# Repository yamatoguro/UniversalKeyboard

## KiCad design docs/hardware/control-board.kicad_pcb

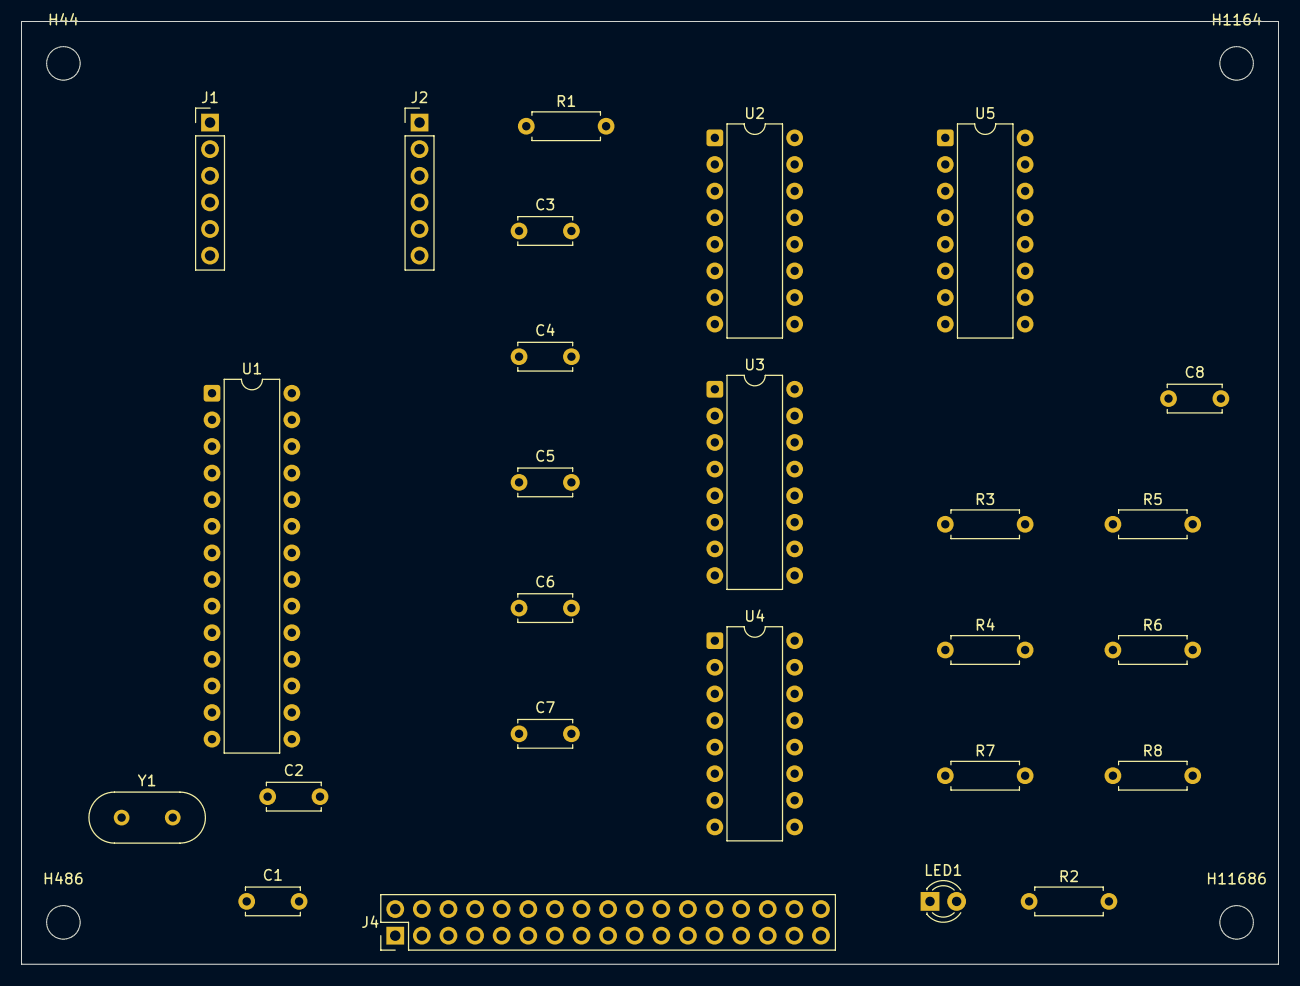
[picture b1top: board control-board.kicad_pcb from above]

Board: 2 copper layers, 120.0 x 90.0 mm, 30 parts (0 on the bottom side), 45 nets, no tracks yet.

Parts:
C1, C2: 22pF; C_Disc_D5.0mm_W2.5mm_P5.00mm
C3, C4, C5, C6, C8: 100nF; C_Disc_D5.0mm_W2.5mm_P5.00mm
C7: 10uF; C_Disc_D5.0mm_W2.5mm_P5.00mm
H44, H486, H1164, H11686: MountingHole; MountingHole_3.2mm_M3
J1, J2: Conn_01x06; PinHeader_1x06_P2.54mm_Vertical
J4: Conn_02x17; PinHeader_2x17_P2.54mm_Vertical
LED1: LED; LED_D3.0mm
R1, R3, R4, R5, R6, R7, R8: 10k; R_Axial_DIN0207_L6.3mm_D2.5mm_P7.62mm_Horizontal
R2: 330R; R_Axial_DIN0207_L6.3mm_D2.5mm_P7.62mm_Horizontal
U1: ATmega328P-PU; DIP-28_W7.62mm
U2, U3, U4: 74HC595; DIP-16_W7.62mm
U5: 74HC165; DIP-16_W7.62mm
Y1: 8MHz; Crystal_HC49-U_Vertical

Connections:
3V3: C3.1, C4.1, C5.1, C6.1, C7.1, C8.1, J1.1, J2.2, J4.30, R1.1, U1.7, U1.20, U1.21, U2.10, U2.16, U3.10, U3.16, U4.10, U4.16, U5.16
COL0: J4.1, U2.15
COL1: J4.2, U2.1
COL2: J4.3, U2.2
COL3: J4.4, U2.3
COL4: J4.5, U2.4
COL5: J4.6, U2.5
COL6: J4.7, U2.6
COL7: J4.8, U2.7
COL8: J4.9, U3.15
COL9: J4.10, U3.1
COL10: J4.11, U3.2
COL11: J4.12, U3.3
COL12: J4.13, U3.4
COL13: J4.14, U3.5
COL14: J4.15, U3.6
COL15: J4.16, U3.7
COL16: J4.17, U4.15
COL17: J4.18, U4.1
COL18: J4.19, U4.2
COL19: J4.20, U4.3
COL20: J4.21, U4.4
COL21: J4.22, U4.5
COL22: J4.23, U4.6
GND: C1.2, C2.2, C3.2, C4.2, C5.2, C6.2, C7.2, C8.2, J1.2, J1.6, J2.3, J4.31, J4.32, J4.33, LED1.1, R3.2, R4.2, R5.2, R6.2, R7.2, R8.2, U1.8, U1.22, U2.8, U2.13, U3.8, U3.13, U4.8, U4.13, U5.5, U5.6, U5.8, U5.10, U5.15
LED_A: LED1.2, R2.2
PI_RX: J1.4, U1.3
PI_TX: J1.3, U1.2
RESET: J2.1, R1.2, U1.1
ROW0: J4.24, R3.1, U5.11
ROW1: J4.25, R4.1, U5.12
ROW2: J4.26, R5.1, U5.13
ROW3: J4.27, R6.1, U5.14
ROW4: J4.28, R7.1, U5.3
ROW5: J4.29, R8.1, U5.4
SR_CASCADE1: U2.9, U3.14
SR_CASCADE2: U3.9, U4.14
SR_CLK: U1.5, U2.11, U3.11, U4.11, U5.2
SR_DATA_IN: U1.12, U5.9
SR_DS: U1.4, U2.14
SR_LATCH: U1.6, U2.12, U3.12, U4.12
SR_LOAD: U1.11, U5.1
STATUS_LED: R2.1, U1.14
XTAL1: C1.1, U1.9, Y1.1
XTAL2: C2.1, U1.10, Y1.2

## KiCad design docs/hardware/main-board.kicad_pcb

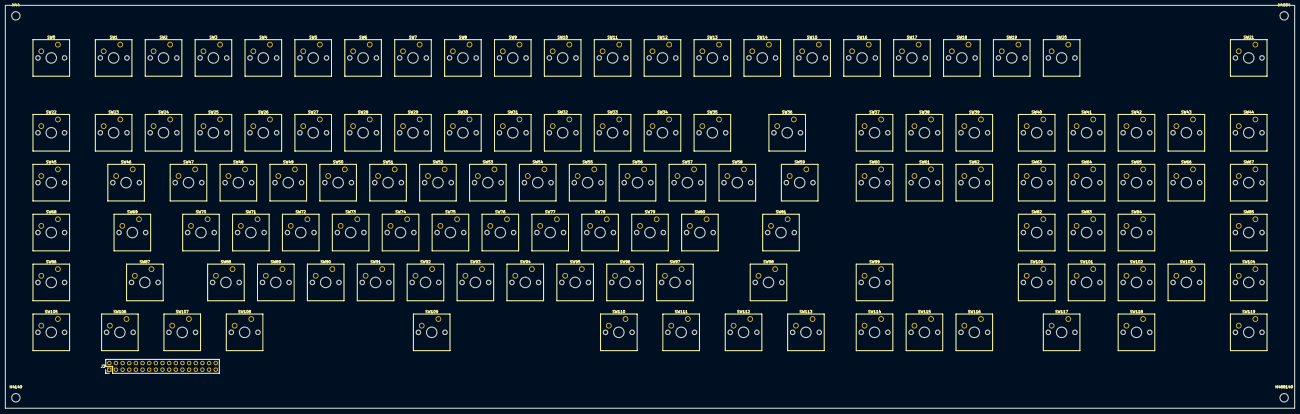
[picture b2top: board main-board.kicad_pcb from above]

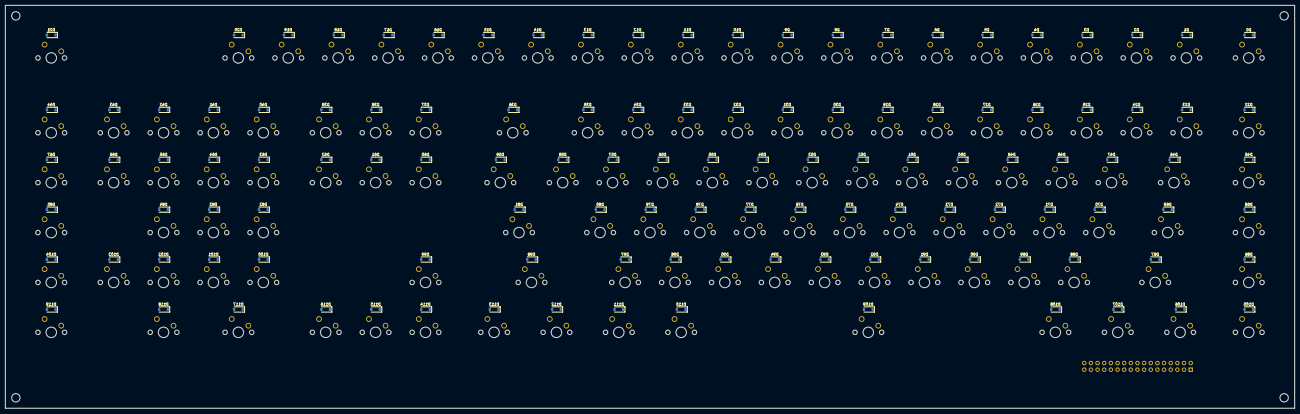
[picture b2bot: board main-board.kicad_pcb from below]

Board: 2 copper layers, 492.2 x 153.8 mm, 245 parts (120 on the bottom side), 150 nets, no tracks yet.

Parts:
D0, D1, D2, D3, D4, D5, D6, D7, D8, D9, D10, D11, D12, D13, D14, D15, D16, D17, D18, D19, D20, D21, D22, D23, D24, D25, D26, D27, D28, D29, D30, D31, D32, D33, D34, D35, D36, D37, D38, D39, D40, D41, D42, D43, D44, D45, D46, D47, D48, D49, D50, D51, D52, D53, D54, D55, D56, D57, D58, D59, D60, D61, D62, D63, D64, D65, D66, D67, D68, D69, D70, D71, D72, D73, D74, D75, D76, D77, D78, D79, D80, D81, D82, D83, D84, D85, D86, D87, D88, D89, D90, D91, D92, D93, D94, D95, D96, D97, D98, D99, D100, D101, D102, D103, D104, D105, D106, D107, D108, D109, D110, D111, D112, D113, D114, D115, D116, D117, D118, D119: BAT54; D_SOD-123
H44, H4149, H4884, H488149: MountingHole; MountingHole_3.2mm_M3
J3: Conn_02x17; PinHeader_2x17_P2.54mm_Vertical
SW0: K_000; SW_Cherry_MX_1.00u_PCB
SW1: K_001; SW_Cherry_MX_1.00u_PCB
SW2: K_002; SW_Cherry_MX_1.00u_PCB
SW3: K_003; SW_Cherry_MX_1.00u_PCB
SW4: K_004; SW_Cherry_MX_1.00u_PCB
SW5: K_005; SW_Cherry_MX_1.00u_PCB
SW6: K_006; SW_Cherry_MX_1.00u_PCB
SW7: K_007; SW_Cherry_MX_1.00u_PCB
SW8: K_008; SW_Cherry_MX_1.00u_PCB
SW9: K_009; SW_Cherry_MX_1.00u_PCB
SW10: K_010; SW_Cherry_MX_1.00u_PCB
SW11: K_011; SW_Cherry_MX_1.00u_PCB
SW12: K_012; SW_Cherry_MX_1.00u_PCB
SW13: K_013; SW_Cherry_MX_1.00u_PCB
SW14: K_014; SW_Cherry_MX_1.00u_PCB
SW15: K_015; SW_Cherry_MX_1.00u_PCB
SW16: K_016; SW_Cherry_MX_1.00u_PCB
SW17: K_017; SW_Cherry_MX_1.00u_PCB
SW18: K_018; SW_Cherry_MX_1.00u_PCB
SW19: K_019; SW_Cherry_MX_1.00u_PCB
SW20: K_020; SW_Cherry_MX_1.00u_PCB
SW21: K_021; SW_Cherry_MX_1.00u_PCB
SW22: K_022; SW_Cherry_MX_1.00u_PCB
SW23: K_023; SW_Cherry_MX_1.00u_PCB
SW24: K_024; SW_Cherry_MX_1.00u_PCB
SW25: K_025; SW_Cherry_MX_1.00u_PCB
SW26: K_026; SW_Cherry_MX_1.00u_PCB
SW27: K_027; SW_Cherry_MX_1.00u_PCB
SW28: K_028; SW_Cherry_MX_1.00u_PCB
SW29: K_029; SW_Cherry_MX_1.00u_PCB
SW30: K_030; SW_Cherry_MX_1.00u_PCB
SW31: K_031; SW_Cherry_MX_1.00u_PCB
SW32: K_032; SW_Cherry_MX_1.00u_PCB
SW33: K_033; SW_Cherry_MX_1.00u_PCB
SW34: K_034; SW_Cherry_MX_1.00u_PCB
SW35: K_035; SW_Cherry_MX_1.00u_PCB
SW36: K_036; SW_Cherry_MX_1.00u_PCB
SW37: K_037; SW_Cherry_MX_1.00u_PCB
SW38: K_038; SW_Cherry_MX_1.00u_PCB
SW39: K_039; SW_Cherry_MX_1.00u_PCB
SW40: K_040; SW_Cherry_MX_1.00u_PCB
SW41: K_041; SW_Cherry_MX_1.00u_PCB
SW42: K_042; SW_Cherry_MX_1.00u_PCB
SW43: K_043; SW_Cherry_MX_1.00u_PCB
SW44: K_044; SW_Cherry_MX_1.00u_PCB
SW45: K_045; SW_Cherry_MX_1.00u_PCB
SW46: K_046; SW_Cherry_MX_1.00u_PCB
SW47: K_047; SW_Cherry_MX_1.00u_PCB
SW48: K_048; SW_Cherry_MX_1.00u_PCB
SW49: K_049; SW_Cherry_MX_1.00u_PCB
SW50: K_050; SW_Cherry_MX_1.00u_PCB
SW51: K_051; SW_Cherry_MX_1.00u_PCB
SW52: K_052; SW_Cherry_MX_1.00u_PCB
SW53: K_053; SW_Cherry_MX_1.00u_PCB
SW54: K_054; SW_Cherry_MX_1.00u_PCB
SW55: K_055; SW_Cherry_MX_1.00u_PCB
SW56: K_056; SW_Cherry_MX_1.00u_PCB
SW57: K_057; SW_Cherry_MX_1.00u_PCB
SW58: K_058; SW_Cherry_MX_1.00u_PCB
SW59: K_059; SW_Cherry_MX_1.00u_PCB
SW60: K_060; SW_Cherry_MX_1.00u_PCB
SW61: K_061; SW_Cherry_MX_1.00u_PCB
SW62: K_062; SW_Cherry_MX_1.00u_PCB
SW63: K_063; SW_Cherry_MX_1.00u_PCB
SW64: K_064; SW_Cherry_MX_1.00u_PCB
SW65: K_065; SW_Cherry_MX_1.00u_PCB
SW66: K_066; SW_Cherry_MX_1.00u_PCB
SW67: K_067; SW_Cherry_MX_1.00u_PCB
SW68: K_068; SW_Cherry_MX_1.00u_PCB
SW69: K_069; SW_Cherry_MX_1.00u_PCB
SW70: K_070; SW_Cherry_MX_1.00u_PCB
SW71: K_071; SW_Cherry_MX_1.00u_PCB
SW72: K_072; SW_Cherry_MX_1.00u_PCB
SW73: K_073; SW_Cherry_MX_1.00u_PCB
SW74: K_074; SW_Cherry_MX_1.00u_PCB
SW75: K_075; SW_Cherry_MX_1.00u_PCB
SW76: K_076; SW_Cherry_MX_1.00u_PCB
SW77: K_077; SW_Cherry_MX_1.00u_PCB
SW78: K_078; SW_Cherry_MX_1.00u_PCB
SW79: K_079; SW_Cherry_MX_1.00u_PCB
SW80: K_080; SW_Cherry_MX_1.00u_PCB
SW81: K_081; SW_Cherry_MX_1.00u_PCB
SW82: K_082; SW_Cherry_MX_1.00u_PCB
SW83: K_083; SW_Cherry_MX_1.00u_PCB
SW84: K_084; SW_Cherry_MX_1.00u_PCB
SW85: K_085; SW_Cherry_MX_1.00u_PCB
SW86: K_086; SW_Cherry_MX_1.00u_PCB
SW87: K_087; SW_Cherry_MX_1.00u_PCB
SW88: K_088; SW_Cherry_MX_1.00u_PCB
SW89: K_089; SW_Cherry_MX_1.00u_PCB
SW90: K_090; SW_Cherry_MX_1.00u_PCB
SW91: K_091; SW_Cherry_MX_1.00u_PCB
SW92: K_092; SW_Cherry_MX_1.00u_PCB
SW93: K_093; SW_Cherry_MX_1.00u_PCB
SW94: K_094; SW_Cherry_MX_1.00u_PCB
SW95: K_095; SW_Cherry_MX_1.00u_PCB
SW96: K_096; SW_Cherry_MX_1.00u_PCB
SW97: K_097; SW_Cherry_MX_1.00u_PCB
SW98: K_098; SW_Cherry_MX_1.00u_PCB
SW99: K_099; SW_Cherry_MX_1.00u_PCB
SW100: K_100; SW_Cherry_MX_1.00u_PCB
SW101: K_101; SW_Cherry_MX_1.00u_PCB
SW102: K_102; SW_Cherry_MX_1.00u_PCB
SW103: K_103; SW_Cherry_MX_1.00u_PCB
SW104: K_104; SW_Cherry_MX_1.00u_PCB
SW105: K_105; SW_Cherry_MX_1.00u_PCB
SW106: K_106; SW_Cherry_MX_1.00u_PCB
SW107: K_107; SW_Cherry_MX_1.00u_PCB
SW108: K_108; SW_Cherry_MX_1.00u_PCB
SW109: K_109; SW_Cherry_MX_1.00u_PCB
SW110: K_110; SW_Cherry_MX_1.00u_PCB
SW111: K_111; SW_Cherry_MX_1.00u_PCB
SW112: K_112; SW_Cherry_MX_1.00u_PCB
SW113: K_113; SW_Cherry_MX_1.00u_PCB
SW114: K_114; SW_Cherry_MX_1.00u_PCB
SW115: K_115; SW_Cherry_MX_1.00u_PCB
SW116: K_116; SW_Cherry_MX_1.00u_PCB
SW117: K_117; SW_Cherry_MX_1.00u_PCB
SW118: K_118; SW_Cherry_MX_1.00u_PCB
SW119: K_119; SW_Cherry_MX_1.00u_PCB

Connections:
COL0: J3.1, SW0.1, SW22.1, SW45.1, SW68.1, SW86.1, SW105.1
COL1: J3.2, SW1.1, SW23.1, SW46.1, SW69.1, SW87.1, SW106.1
COL2: J3.3, SW2.1, SW24.1, SW47.1, SW70.1, SW88.1, SW107.1
COL3: J3.4, SW3.1, SW25.1, SW48.1, SW71.1, SW89.1, SW108.1
COL4: J3.5, SW4.1, SW26.1, SW49.1, SW72.1, SW90.1, SW109.1
COL5: J3.6, SW5.1, SW27.1, SW50.1, SW73.1, SW91.1, SW110.1
COL6: J3.7, SW6.1, SW28.1, SW51.1, SW74.1, SW92.1, SW111.1
COL7: J3.8, SW7.1, SW29.1, SW52.1, SW75.1, SW93.1, SW112.1
COL8: J3.9, SW8.1, SW30.1, SW53.1, SW76.1, SW94.1, SW113.1
COL9: J3.10, SW9.1, SW31.1, SW54.1, SW77.1, SW95.1, SW114.1
COL10: J3.11, SW10.1, SW32.1, SW55.1, SW78.1, SW96.1, SW115.1
COL11: J3.12, SW11.1, SW33.1, SW56.1, SW79.1, SW97.1, SW116.1
COL12: J3.13, SW12.1, SW34.1, SW57.1, SW80.1, SW98.1, SW117.1
COL13: J3.14, SW13.1, SW35.1, SW58.1, SW81.1, SW99.1, SW118.1
COL14: J3.15, SW14.1, SW36.1, SW59.1, SW82.1, SW100.1, SW119.1
COL15: J3.16, SW15.1, SW37.1, SW60.1, SW83.1, SW101.1
COL16: J3.17, SW16.1, SW38.1, SW61.1, SW84.1, SW102.1
COL17: J3.18, SW17.1, SW39.1, SW62.1, SW85.1, SW103.1
COL18: J3.19, SW18.1, SW40.1, SW63.1, SW104.1
COL19: J3.20, SW19.1, SW41.1, SW64.1
COL20: J3.21, SW20.1, SW42.1, SW65.1
COL21: J3.22, SW21.1, SW43.1, SW66.1
COL22: J3.23, SW44.1, SW67.1
GND: J3.31, J3.32, J3.33
KEY0: D0.2, SW0.2
KEY1: D1.2, SW1.2
KEY2: D2.2, SW2.2
KEY3: D3.2, SW3.2
KEY4: D4.2, SW4.2
KEY5: D5.2, SW5.2
KEY6: D6.2, SW6.2
KEY7: D7.2, SW7.2
KEY8: D8.2, SW8.2
KEY9: D9.2, SW9.2
KEY10: D10.2, SW10.2
KEY11: D11.2, SW11.2
KEY12: D12.2, SW12.2
KEY13: D13.2, SW13.2
KEY14: D14.2, SW14.2
KEY15: D15.2, SW15.2
KEY16: D16.2, SW16.2
KEY17: D17.2, SW17.2
KEY18: D18.2, SW18.2
KEY19: D19.2, SW19.2
KEY20: D20.2, SW20.2
KEY21: D21.2, SW21.2
KEY22: D22.2, SW22.2
KEY23: D23.2, SW23.2
KEY24: D24.2, SW24.2
KEY25: D25.2, SW25.2
KEY26: D26.2, SW26.2
KEY27: D27.2, SW27.2
KEY28: D28.2, SW28.2
KEY29: D29.2, SW29.2
KEY30: D30.2, SW30.2
KEY31: D31.2, SW31.2
KEY32: D32.2, SW32.2
KEY33: D33.2, SW33.2
KEY34: D34.2, SW34.2
KEY35: D35.2, SW35.2
KEY36: D36.2, SW36.2
KEY37: D37.2, SW37.2
KEY38: D38.2, SW38.2
KEY39: D39.2, SW39.2
KEY40: D40.2, SW40.2
KEY41: D41.2, SW41.2
KEY42: D42.2, SW42.2
KEY43: D43.2, SW43.2
KEY44: D44.2, SW44.2
KEY45: D45.2, SW45.2
KEY46: D46.2, SW46.2
KEY47: D47.2, SW47.2
KEY48: D48.2, SW48.2
KEY49: D49.2, SW49.2
KEY50: D50.2, SW50.2
KEY51: D51.2, SW51.2
KEY52: D52.2, SW52.2
KEY53: D53.2, SW53.2
KEY54: D54.2, SW54.2
KEY55: D55.2, SW55.2
KEY56: D56.2, SW56.2
KEY57: D57.2, SW57.2
KEY58: D58.2, SW58.2
KEY59: D59.2, SW59.2
KEY60: D60.2, SW60.2
KEY61: D61.2, SW61.2
KEY62: D62.2, SW62.2
KEY63: D63.2, SW63.2
KEY64: D64.2, SW64.2
KEY65: D65.2, SW65.2
KEY66: D66.2, SW66.2
KEY67: D67.2, SW67.2
KEY68: D68.2, SW68.2
KEY69: D69.2, SW69.2
KEY70: D70.2, SW70.2
KEY71: D71.2, SW71.2
KEY72: D72.2, SW72.2
KEY73: D73.2, SW73.2
KEY74: D74.2, SW74.2
KEY75: D75.2, SW75.2
KEY76: D76.2, SW76.2
KEY77: D77.2, SW77.2
KEY78: D78.2, SW78.2
KEY79: D79.2, SW79.2
KEY80: D80.2, SW80.2
KEY81: D81.2, SW81.2
KEY82: D82.2, SW82.2
KEY83: D83.2, SW83.2
KEY84: D84.2, SW84.2
KEY85: D85.2, SW85.2
KEY86: D86.2, SW86.2
KEY87: D87.2, SW87.2
KEY88: D88.2, SW88.2
KEY89: D89.2, SW89.2
KEY90: D90.2, SW90.2
KEY91: D91.2, SW91.2
KEY92: D92.2, SW92.2
KEY93: D93.2, SW93.2
KEY94: D94.2, SW94.2
KEY95: D95.2, SW95.2
KEY96: D96.2, SW96.2
KEY97: D97.2, SW97.2
KEY98: D98.2, SW98.2
KEY99: D99.2, SW99.2
KEY100: D100.2, SW100.2
KEY101: D101.2, SW101.2
KEY102: D102.2, SW102.2
KEY103: D103.2, SW103.2
KEY104: D104.2, SW104.2
KEY105: D105.2, SW105.2
KEY106: D106.2, SW106.2
KEY107: D107.2, SW107.2
KEY108: D108.2, SW108.2
KEY109: D109.2, SW109.2
KEY110: D110.2, SW110.2
KEY111: D111.2, SW111.2
KEY112: D112.2, SW112.2
KEY113: D113.2, SW113.2
KEY114: D114.2, SW114.2
KEY115: D115.2, SW115.2
KEY116: D116.2, SW116.2
KEY117: D117.2, SW117.2
KEY118: D118.2, SW118.2
KEY119: D119.2, SW119.2
ROW0: D0.1, D1.1, D2.1, D3.1, D4.1, D5.1, D6.1, D7.1, D8.1, D9.1, D10.1, D11.1, D12.1, D13.1, D14.1, D15.1, D16.1, D17.1, D18.1, D19.1, D20.1, D21.1, J3.24
ROW1: D22.1, D23.1, D24.1, D25.1, D26.1, D27.1, D28.1, D29.1, D30.1, D31.1, D32.1, D33.1, D34.1, D35.1, D36.1, D37.1, D38.1, D39.1, D40.1, D41.1, D42.1, D43.1, D44.1, J3.25
ROW2: D45.1, D46.1, D47.1, D48.1, D49.1, D50.1, D51.1, D52.1, D53.1, D54.1, D55.1, D56.1, D57.1, D58.1, D59.1, D60.1, D61.1, D62.1, D63.1, D64.1, D65.1, D66.1, D67.1, J3.26
ROW3: D68.1, D69.1, D70.1, D71.1, D72.1, D73.1, D74.1, D75.1, D76.1, D77.1, D78.1, D79.1, D80.1, D81.1, D82.1, D83.1, D84.1, D85.1, J3.27
ROW4: D86.1, D87.1, D88.1, D89.1, D90.1, D91.1, D92.1, D93.1, D94.1, D95.1, D96.1, D97.1, D98.1, D99.1, D100.1, D101.1, D102.1, D103.1, D104.1, J3.28
ROW5: D105.1, D106.1, D107.1, D108.1, D109.1, D110.1, D111.1, D112.1, D113.1, D114.1, D115.1, D116.1, D117.1, D118.1, D119.1, J3.29

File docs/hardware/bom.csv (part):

ref,value,footprint,description
U1,ATmega328P-PU,Package_DIP:DIP-28_W7.62mm,MCU AVR 32KB @ 3V3/8MHz (cristal)
U2,74HC595,Package_DIP:DIP-16_W7.62mm,Colunas 0-7
U3,74HC595,Package_DIP:DIP-16_W7.62mm,Colunas 8-15
U4,74HC595,Package_DIP:DIP-16_W7.62mm,Colunas 16-22
U5,74HC165,Package_DIP:DIP-16_W7.62mm,Linhas 0-5
Y1,8MHz,Crystal:Crystal_HC49-U_Vertical,Cristal 8MHz
C1,22pF,Capacitor_THT:C_Disc_D5.0mm_W2.5mm_P5.00mm,Carga do cristal
C2,22pF,Capacitor_THT:C_Disc_D5.0mm_W2.5mm_P5.00mm,Carga do cristal
C3,100nF,Capacitor_THT:C_Disc_D5.0mm_W2.5mm_P5.00mm,Desacoplamento U1
C4,100nF,Capacitor_THT:C_Disc_D5.0mm_W2.5mm_P5.00mm,Desacoplamento U2
C5,100nF,Capacitor_THT:C_Disc_D5.0mm_W2.5mm_P5.00mm,Desacoplamento U3
C6,100nF,Capacitor_THT:C_Disc_D5.0mm_W2.5mm_P5.00mm,Desacoplamento U4
C8,100nF,Capacitor_THT:C_Disc_D5.0mm_W2.5mm_P5.00mm,Desacoplamento U5
C7,10uF,Capacitor_THT:CP_Radial_D5.0mm_P2.00mm,Bulk da rail 3V3
R1,10k,Resistor_THT:R_Axial_DIN0207_L6.3mm_D2.5mm_P7.62mm,Pull-up de RESET
R2,330R,Resistor_THT:R_Axial_DIN0207_L6.3mm_D2.5mm_P7.62mm,Serie do LED de status
R3,10k,Resistor_THT:R_Axial_DIN0207_L6.3mm_D2.5mm_P7.62mm,Pull-down da ROW0
R4,10k,Resistor_THT:R_Axial_DIN0207_L6.3mm_D2.5mm_P7.62mm,Pull-down da ROW1
R5,10k,Resistor_THT:R_Axial_DIN0207_L6.3mm_D2.5mm_P7.62mm,Pull-down da ROW2
R6,10k,Resistor_THT:R_Axial_DIN0207_L6.3mm_D2.5mm_P7.62mm,Pull-down da ROW3
R7,10k,Resistor_THT:R_Axial_DIN0207_L6.3mm_D2.5mm_P7.62mm,Pull-down da ROW4
R8,10k,Resistor_THT:R_Axial_DIN0207_L6.3mm_D2.5mm_P7.62mm,Pull-down da ROW5
LED1,LED,LED_THT:LED_D3.0mm,Status do link
J1,Conn_01x06,Connector_PinHeader_2.54mm:PinHeader_1x06_P2.54mm_Vertical,"Link Pi: 3V3, GND, PiTX, PiRX, spare, GND"
J2,Conn_01x06,Connector_PinHeader_2.54mm:PinHeader_1x06_P2.54mm_Vertical,"ICSP: RESET, 3V3, GND e debug"
J3,Conn_02x17,Connector_PinHeader_2.54mm:PinHeader_2x17_P2.54mm_Vertical,Interligacao para a placa de controle (lado matriz)
J4,Conn_02x17,Connector_PinHeader_2.54mm:PinHeader_2x17_P2.54mm_Vertical,Interligacao para a placa da matriz (lado controle)
SW0,K_000,Switch:SW_Push,Tecla 0 (c0 r0)
SW1,K_001,Switch:SW_Push,Tecla 1 (c1 r0)
SW2,K_002,Switch:SW_Push,Tecla 2 (c2 r0)
SW3,K_003,Switch:SW_Push,Tecla 3 (c3 r0)
SW4,K_004,Switch:SW_Push,Tecla 4 (c4 r0)
SW5,K_005,Switch:SW_Push,Tecla 5 (c5 r0)
SW6,K_006,Switch:SW_Push,Tecla 6 (c6 r0)
SW7,K_007,Switch:SW_Push,Tecla 7 (c7 r0)
SW8,K_008,Switch:SW_Push,Tecla 8 (c8 r0)
SW9,K_009,Switch:SW_Push,Tecla 9 (c9 r0)
SW10,K_010,Switch:SW_Push,Tecla 10 (c10 r0)
SW11,K_011,Switch:SW_Push,Tecla 11 (c11 r0)
SW12,K_012,Switch:SW_Push,Tecla 12 (c12 r0)
SW13,K_013,Switch:SW_Push,Tecla 13 (c13 r0)
SW14,K_014,Switch:SW_Push,Tecla 14 (c14 r0)
SW15,K_015,Switch:SW_Push,Tecla 15 (c15 r0)
SW16,K_016,Switch:SW_Push,Tecla 16 (c16 r0)
SW17,K_017,Switch:SW_Push,Tecla 17 (c17 r0)
SW18,K_018,Switch:SW_Push,Tecla 18 (c18 r0)
SW19,K_019,Switch:SW_Push,Tecla 19 (c19 r0)
SW20,K_020,Switch:SW_Push,Tecla 20 (c20 r0)
SW21,K_021,Switch:SW_Push,Tecla 21 (c21 r0)
SW22,K_022,Switch:SW_Push,Tecla 22 (c0 r1)
SW23,K_023,Switch:SW_Push,Tecla 23 (c1 r1)
SW24,K_024,Switch:SW_Push,Tecla 24 (c2 r1)
SW25,K_025,Switch:SW_Push,Tecla 25 (c3 r1)
SW26,K_026,Switch:SW_Push,Tecla 26 (c4 r1)
SW27,K_027,Switch:SW_Push,Tecla 27 (c5 r1)
SW28,K_028,Switch:SW_Push,Tecla 28 (c6 r1)
SW29,K_029,Switch:SW_Push,Tecla 29 (c7 r1)
SW30,K_030,Switch:SW_Push,Tecla 30 (c8 r1)
SW31,K_031,Switch:SW_Push,Tecla 31 (c9 r1)
SW32,K_032,Switch:SW_Push,Tecla 32 (c10 r1)
SW33,K_033,Switch:SW_Push,Tecla 33 (c11 r1)
SW34,K_034,Switch:SW_Push,Tecla 34 (c12 r1)
SW35,K_035,Switch:SW_Push,Tecla 35 (c13 r1)
SW36,K_036,Switch:SW_Push,Tecla 36 (c14 r1)
SW37,K_037,Switch:SW_Push,Tecla 37 (c15 r1)
SW38,K_038,Switch:SW_Push,Tecla 38 (c16 r1)
SW39,K_039,Switch:SW_Push,Tecla 39 (c17 r1)
SW40,K_040,Switch:SW_Push,Tecla 40 (c18 r1)
SW41,K_041,Switch:SW_Push,Tecla 41 (c19 r1)
SW42,K_042,Switch:SW_Push,Tecla 42 (c20 r1)
SW43,K_043,Switch:SW_Push,Tecla 43 (c21 r1)
SW44,K_044,Switch:SW_Push,Tecla 44 (c22 r1)
SW45,K_045,Switch:SW_Push,Tecla 45 (c0 r2)
SW46,K_046,Switch:SW_Push,Tecla 46 (c1 r2)
SW47,K_047,Switch:SW_Push,Tecla 47 (c2 r2)
SW48,K_048,Switch:SW_Push,Tecla 48 (c3 r2)
SW49,K_049,Switch:SW_Push,Tecla 49 (c4 r2)
SW50,K_050,Switch:SW_Push,Tecla 50 (c5 r2)
SW51,K_051,Switch:SW_Push,Tecla 51 (c6 r2)
SW52,K_052,Switch:SW_Push,Tecla 52 (c7 r2)
SW53,K_053,Switch:SW_Push,Tecla 53 (c8 r2)
SW54,K_054,Switch:SW_Push,Tecla 54 (c9 r2)
SW55,K_055,Switch:SW_Push,Tecla 55 (c10 r2)
SW56,K_056,Switch:SW_Push,Tecla 56 (c11 r2)
SW57,K_057,Switch:SW_Push,Tecla 57 (c12 r2)
SW58,K_058,Switch:SW_Push,Tecla 58 (c13 r2)
SW59,K_059,Switch:SW_Push,Tecla 59 (c14 r2)
SW60,K_060,Switch:SW_Push,Tecla 60 (c15 r2)
SW61,K_061,Switch:SW_Push,Tecla 61 (c16 r2)
SW62,K_062,Switch:SW_Push,Tecla 62 (c17 r2)
SW63,K_063,Switch:SW_Push,Tecla 63 (c18 r2)
SW64,K_064,Switch:SW_Push,Tecla 64 (c19 r2)
SW65,K_065,Switch:SW_Push,Tecla 65 (c20 r2)
SW66,K_066,Switch:SW_Push,Tecla 66 (c21 r2)
SW67,K_067,Switch:SW_Push,Tecla 67 (c22 r2)
SW68,K_068,Switch:SW_Push,Tecla 68 (c0 r3)
SW69,K_069,Switch:SW_Push,Tecla 69 (c1 r3)
SW70,K_070,Switch:SW_Push,Tecla 70 (c2 r3)
SW71,K_071,Switch:SW_Push,Tecla 71 (c3 r3)
SW72,K_072,Switch:SW_Push,Tecla 72 (c4 r3)
SW73,K_073,Switch:SW_Push,Tecla 73 (c5 r3)
SW74,K_074,Switch:SW_Push,Tecla 74 (c6 r3)
SW75,K_075,Switch:SW_Push,Tecla 75 (c7 r3)
SW76,K_076,Switch:SW_Push,Tecla 76 (c8 r3)
SW77,K_077,Switch:SW_Push,Tecla 77 (c9 r3)
SW78,K_078,Switch:SW_Push,Tecla 78 (c10 r3)
SW79,K_079,Switch:SW_Push,Tecla 79 (c11 r3)
SW80,K_080,Switch:SW_Push,Tecla 80 (c12 r3)
SW81,K_081,Switch:SW_Push,Tecla 81 (c13 r3)
SW82,K_082,Switch:SW_Push,Tecla 82 (c14 r3)
SW83,K_083,Switch:SW_Push,Tecla 83 (c15 r3)
SW84,K_084,Switch:SW_Push,Tecla 84 (c16 r3)
SW85,K_085,Switch:SW_Push,Tecla 85 (c17 r3)
SW86,K_086,Switch:SW_Push,Tecla 86 (c0 r4)
SW87,K_087,Switch:SW_Push,Tecla 87 (c1 r4)
SW88,K_088,Switch:SW_Push,Tecla 88 (c2 r4)
SW89,K_089,Switch:SW_Push,Tecla 89 (c3 r4)
SW90,K_090,Switch:SW_Push,Tecla 90 (c4 r4)
SW91,K_091,Switch:SW_Push,Tecla 91 (c5 r4)
SW92,K_092,Switch:SW_Push,Tecla 92 (c6 r4)
SW93,K_093,Switch:SW_Push,Tecla 93 (c7 r4)
SW94,K_094,Switch:SW_Push,Tecla 94 (c8 r4)
SW95,K_095,Switch:SW_Push,Tecla 95 (c9 r4)
SW96,K_096,Switch:SW_Push,Tecla 96 (c10 r4)
SW97,K_097,Switch:SW_Push,Tecla 97 (c11 r4)
SW98,K_098,Switch:SW_Push,Tecla 98 (c12 r4)
SW99,K_099,Switch:SW_Push,Tecla 99 (c13 r4)
SW100,K_100,Switch:SW_Push,Tecla 100 (c14 r4)
SW101,K_101,Switch:SW_Push,Tecla 101 (c15 r4)
SW102,K_102,Switch:SW_Push,Tecla 102 (c16 r4)
SW103,K_103,Switch:SW_Push,Tecla 103 (c17 r4)
SW104,K_104,Switch:SW_Push,Tecla 104 (c18 r4)
SW105,K_105,Switch:SW_Push,Tecla 105 (c0 r5)
SW106,K_106,Switch:SW_Push,Tecla 106 (c1 r5)
SW107,K_107,Switch:SW_Push,Tecla 107 (c2 r5)
SW108,K_108,Switch:SW_Push,Tecla 108 (c3 r5)
SW109,K_109,Switch:SW_Push,Tecla 109 (c4 r5)
SW110,K_110,Switch:SW_Push,Tecla 110 (c5 r5)
SW111,K_111,Switch:SW_Push,Tecla 111 (c6 r5)
SW112,K_112,Switch:SW_Push,Tecla 112 (c7 r5)
SW113,K_113,Switch:SW_Push,Tecla 113 (c8 r5)
SW114,K_114,Switch:SW_Push,Tecla 114 (c9 r5)
SW115,K_115,Switch:SW_Push,Tecla 115 (c10 r5)
SW116,K_116,Switch:SW_Push,Tecla 116 (c11 r5)
SW117,K_117,Switch:SW_Push,Tecla 117 (c12 r5)
SW118,K_118,Switch:SW_Push,Tecla 118 (c13 r5)
SW119,K_119,Switch:SW_Push,Tecla 119 (c14 r5)
D0,BAT54,Diode_SMD:D_SOD-123,Anti-ghosting da tecla 0
D1,BAT54,Diode_SMD:D_SOD-123,Anti-ghosting da tecla 1
D2,BAT54,Diode_SMD:D_SOD-123,Anti-ghosting da tecla 2
D3,BAT54,Diode_SMD:D_SOD-123,Anti-ghosting da tecla 3
D4,BAT54,Diode_SMD:D_SOD-123,Anti-ghosting da tecla 4
D5,BAT54,Diode_SMD:D_SOD-123,Anti-ghosting da tecla 5
D6,BAT54,Diode_SMD:D_SOD-123,Anti-ghosting da tecla 6
D7,BAT54,Diode_SMD:D_SOD-123,Anti-ghosting da tecla 7
D8,BAT54,Diode_SMD:D_SOD-123,Anti-ghosting da tecla 8
D9,BAT54,Diode_SMD:D_SOD-123,Anti-ghosting da tecla 9
D10,BAT54,Diode_SMD:D_SOD-123,Anti-ghosting da tecla 10
D11,BAT54,Diode_SMD:D_SOD-123,Anti-ghosting da tecla 11
D12,BAT54,Diode_SMD:D_SOD-123,Anti-ghosting da tecla 12
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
